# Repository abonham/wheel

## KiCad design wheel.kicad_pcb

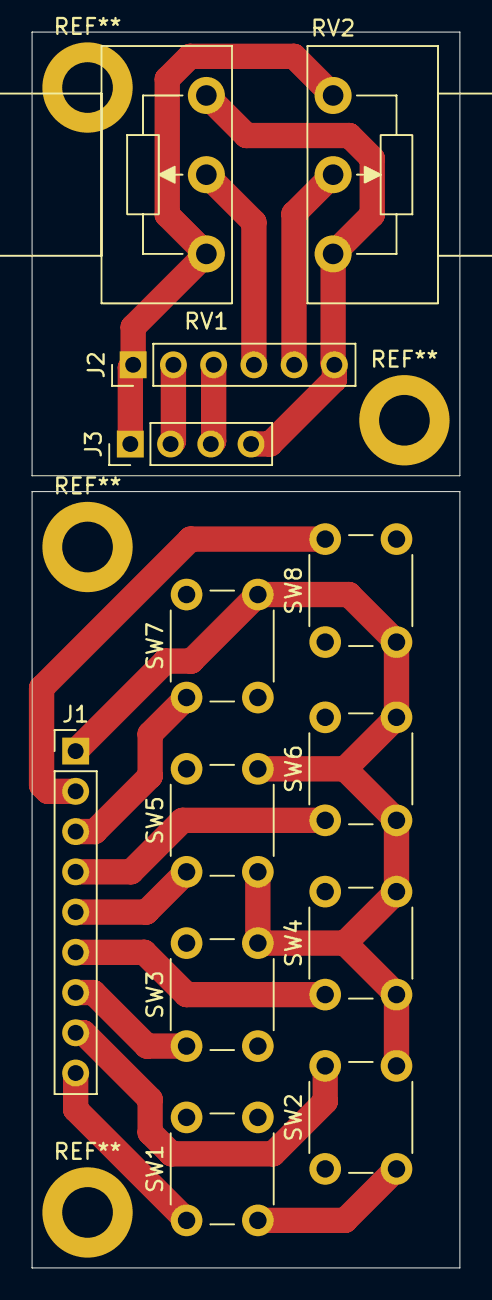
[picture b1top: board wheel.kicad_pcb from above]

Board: 2 copper layers, 27.0 x 78.0 mm, 13 parts (0 on the bottom side), 14 nets.

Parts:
J1: Conn_01x09; PinHeader_1x09_P2.54mm_Vertical
J2: Conn_01x06_Socket; PinHeader_1x06_P2.54mm_Vertical
J3: Conn_01x04_Socket; PinHeader_1x04_P2.54mm_Vertical
RV1, RV2: R_Potentiometer; Potentiometer_Piher_PC-16_Single_Horizontal
SW1, SW2, SW3, SW4, SW5, SW6, SW7, SW8: SW_DPST; SW_PUSH_6mm

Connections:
5V: J2.6, J3.4, RV1.1, RV2.1
/Buttons/A: J1.2, SW8.1
/Buttons/B: J1.3, SW7.1
/Buttons/LB: J1.6, SW4.1
/Buttons/LT: J1.7, SW3.1
/Buttons/RB: J1.8, SW2.1
/Buttons/RT: J1.9, SW1.1
/Buttons/X: J1.4, SW6.1
/Buttons/Y: J1.5, SW5.1
A: J2.2, J3.2
Accelerator: J2.4, RV1.2
B: J2.3, J3.3
Brake: J2.5, RV2.2
GND: J1.1, J2.1, J3.1, RV1.3, RV2.3, SW1.2, SW2.2, SW3.2, SW4.2, SW5.2, SW6.2, SW7.2, SW8.2

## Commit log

2024-11-11 initial
2024-11-12 generate gerbers
2024-11-12 start cnc
2024-11-12 create drill job
2024-11-12 gerber
2024-11-13 cnc files
2024-12-04 ignore backups
2024-12-17 add firmware
2025-01-01 latest
2025-01-01 switch to using PIO for rotary encoder
2025-01-06 generally working
2025-01-06 try to split hid report
2025-01-06 working as plain controller
2025-01-06 aligned hat report
